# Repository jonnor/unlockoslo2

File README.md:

# Goals

* This is a development board. Should be safe to handle and easy to
  use.

## Non-goals

* Low-power operation

# Datasheets

* https://www.silabs.com/documents/public/data-sheets/cp2102n-datasheet.pdf
* https://www.silabs.com/documents/public/application-notes/an721.pdf

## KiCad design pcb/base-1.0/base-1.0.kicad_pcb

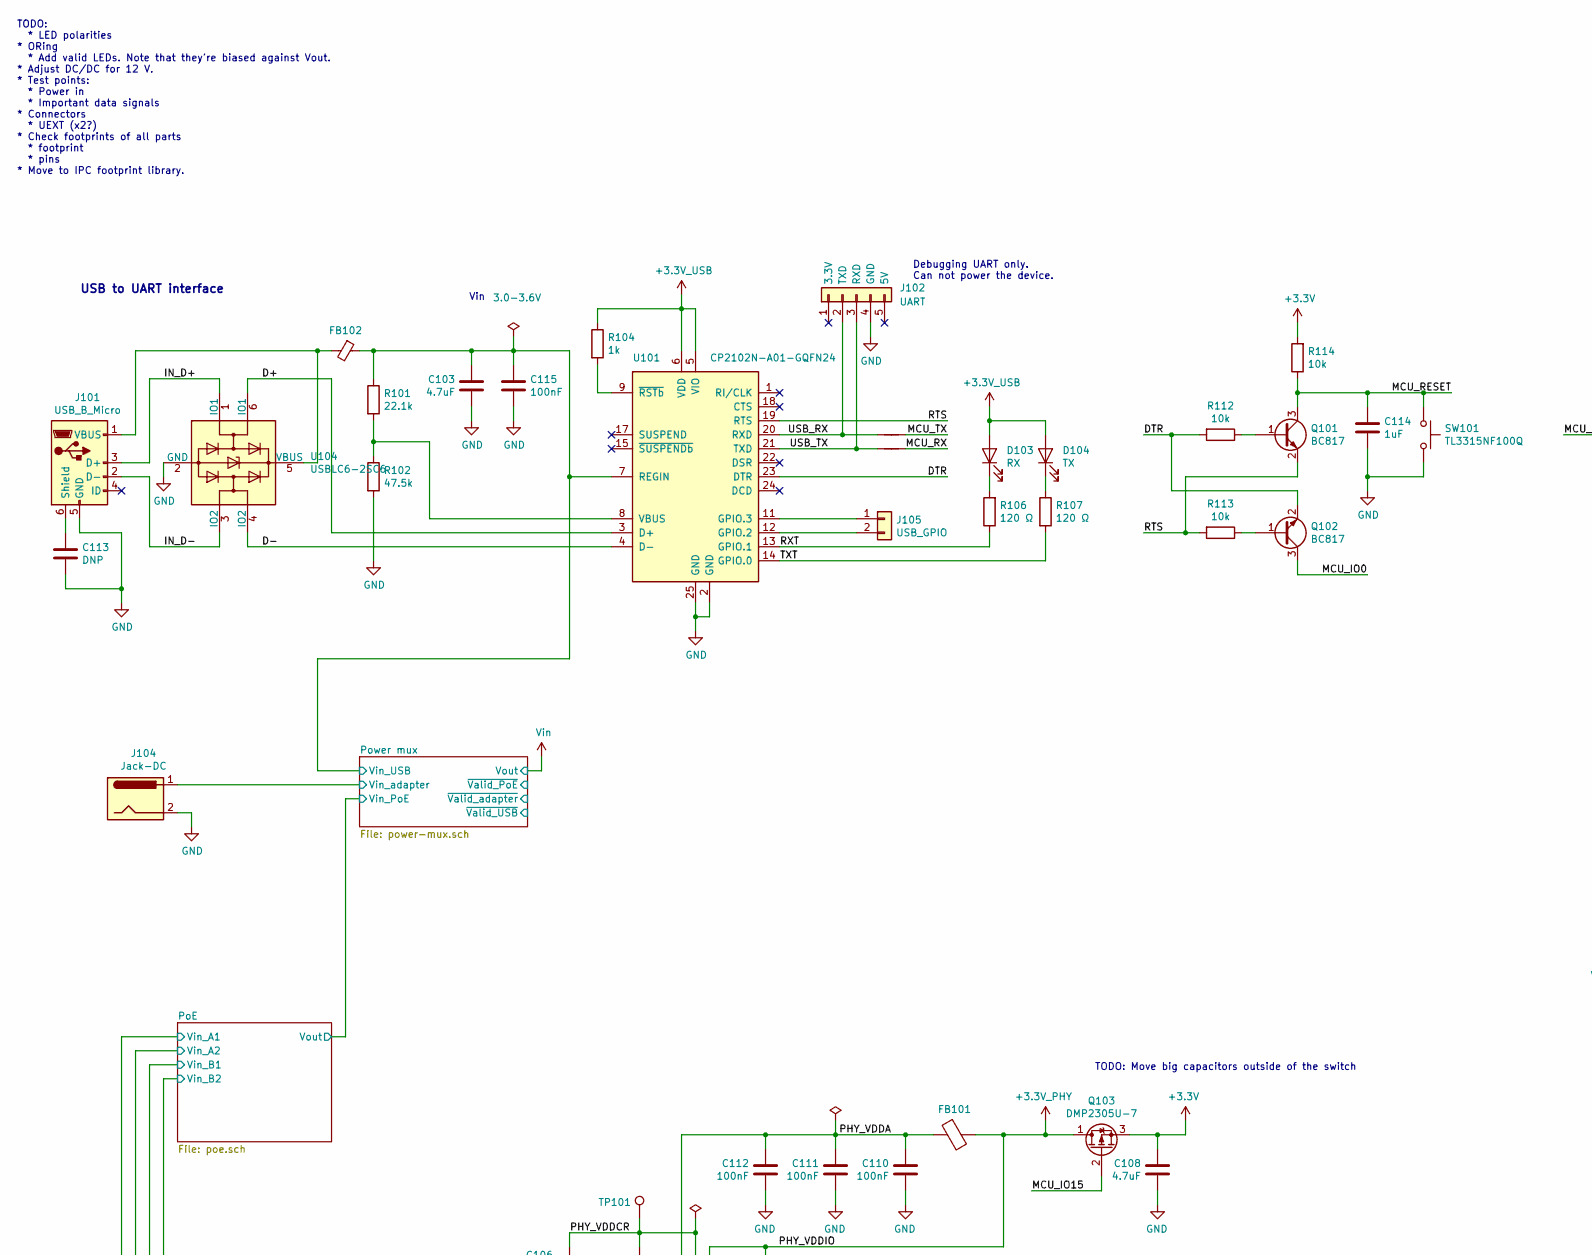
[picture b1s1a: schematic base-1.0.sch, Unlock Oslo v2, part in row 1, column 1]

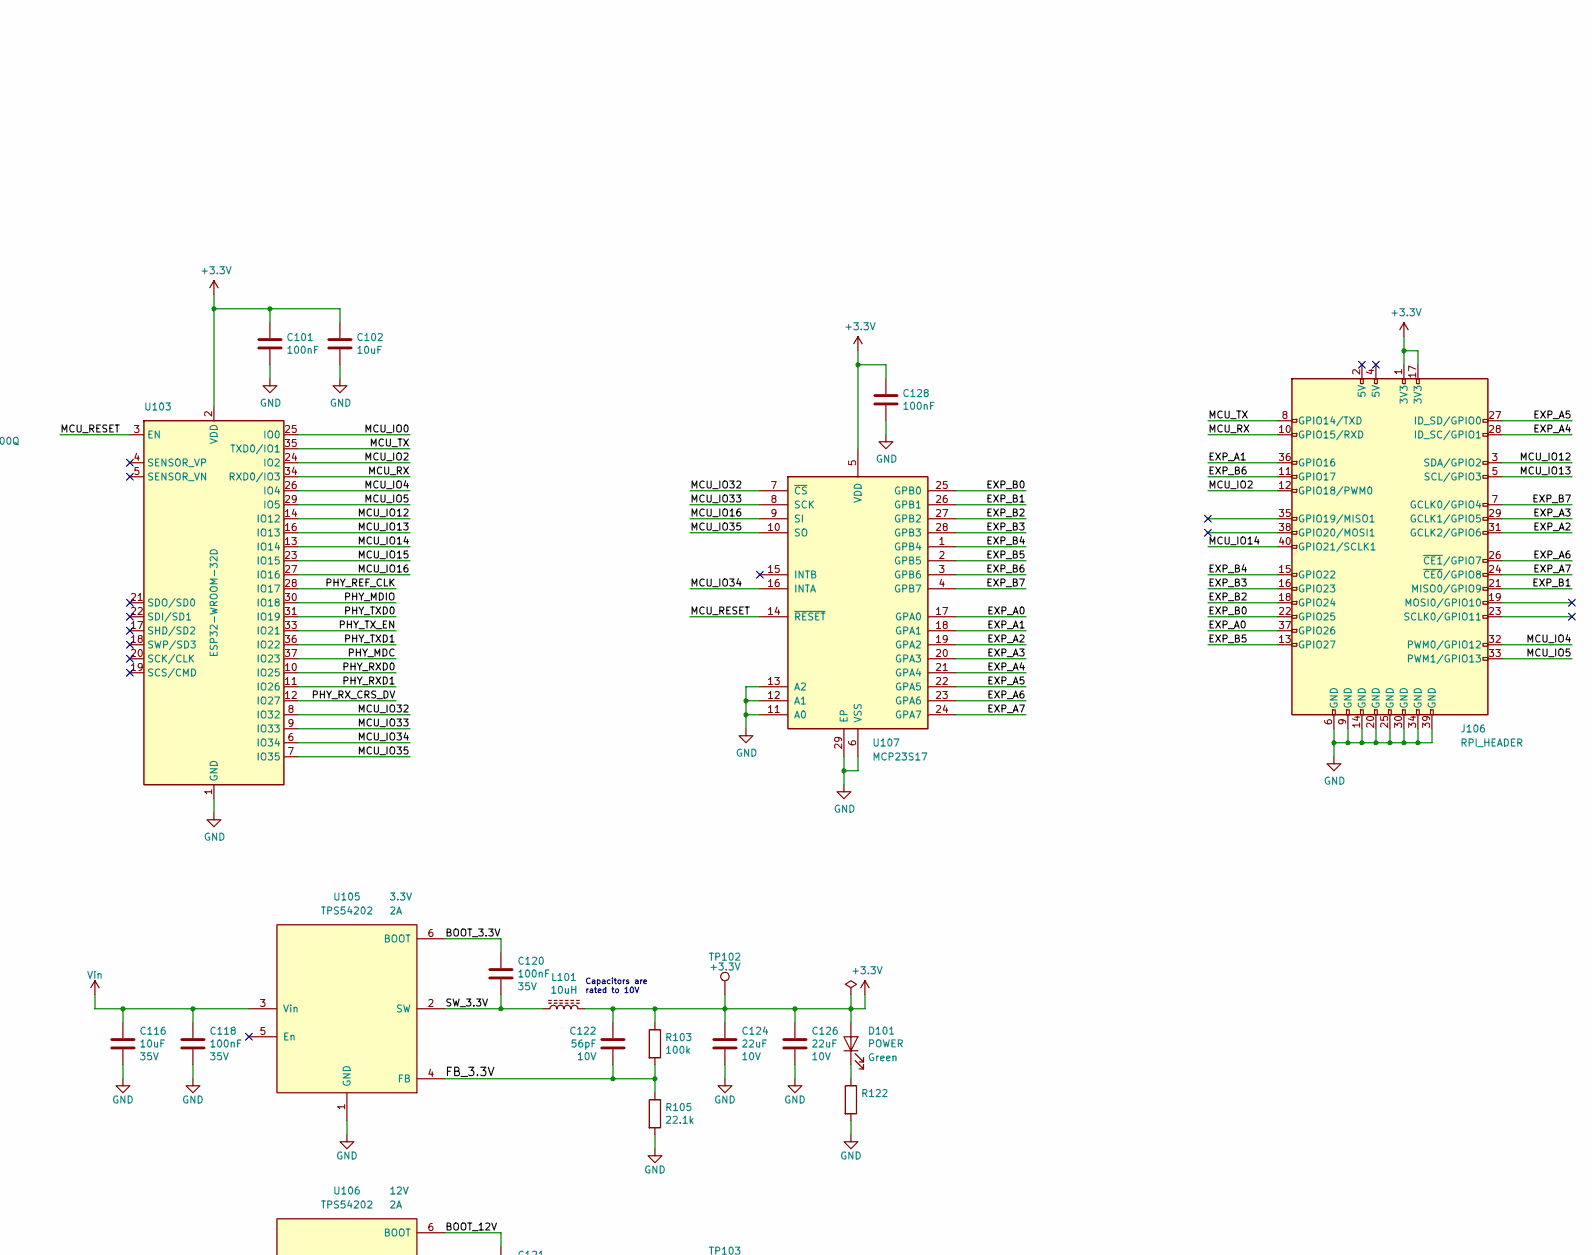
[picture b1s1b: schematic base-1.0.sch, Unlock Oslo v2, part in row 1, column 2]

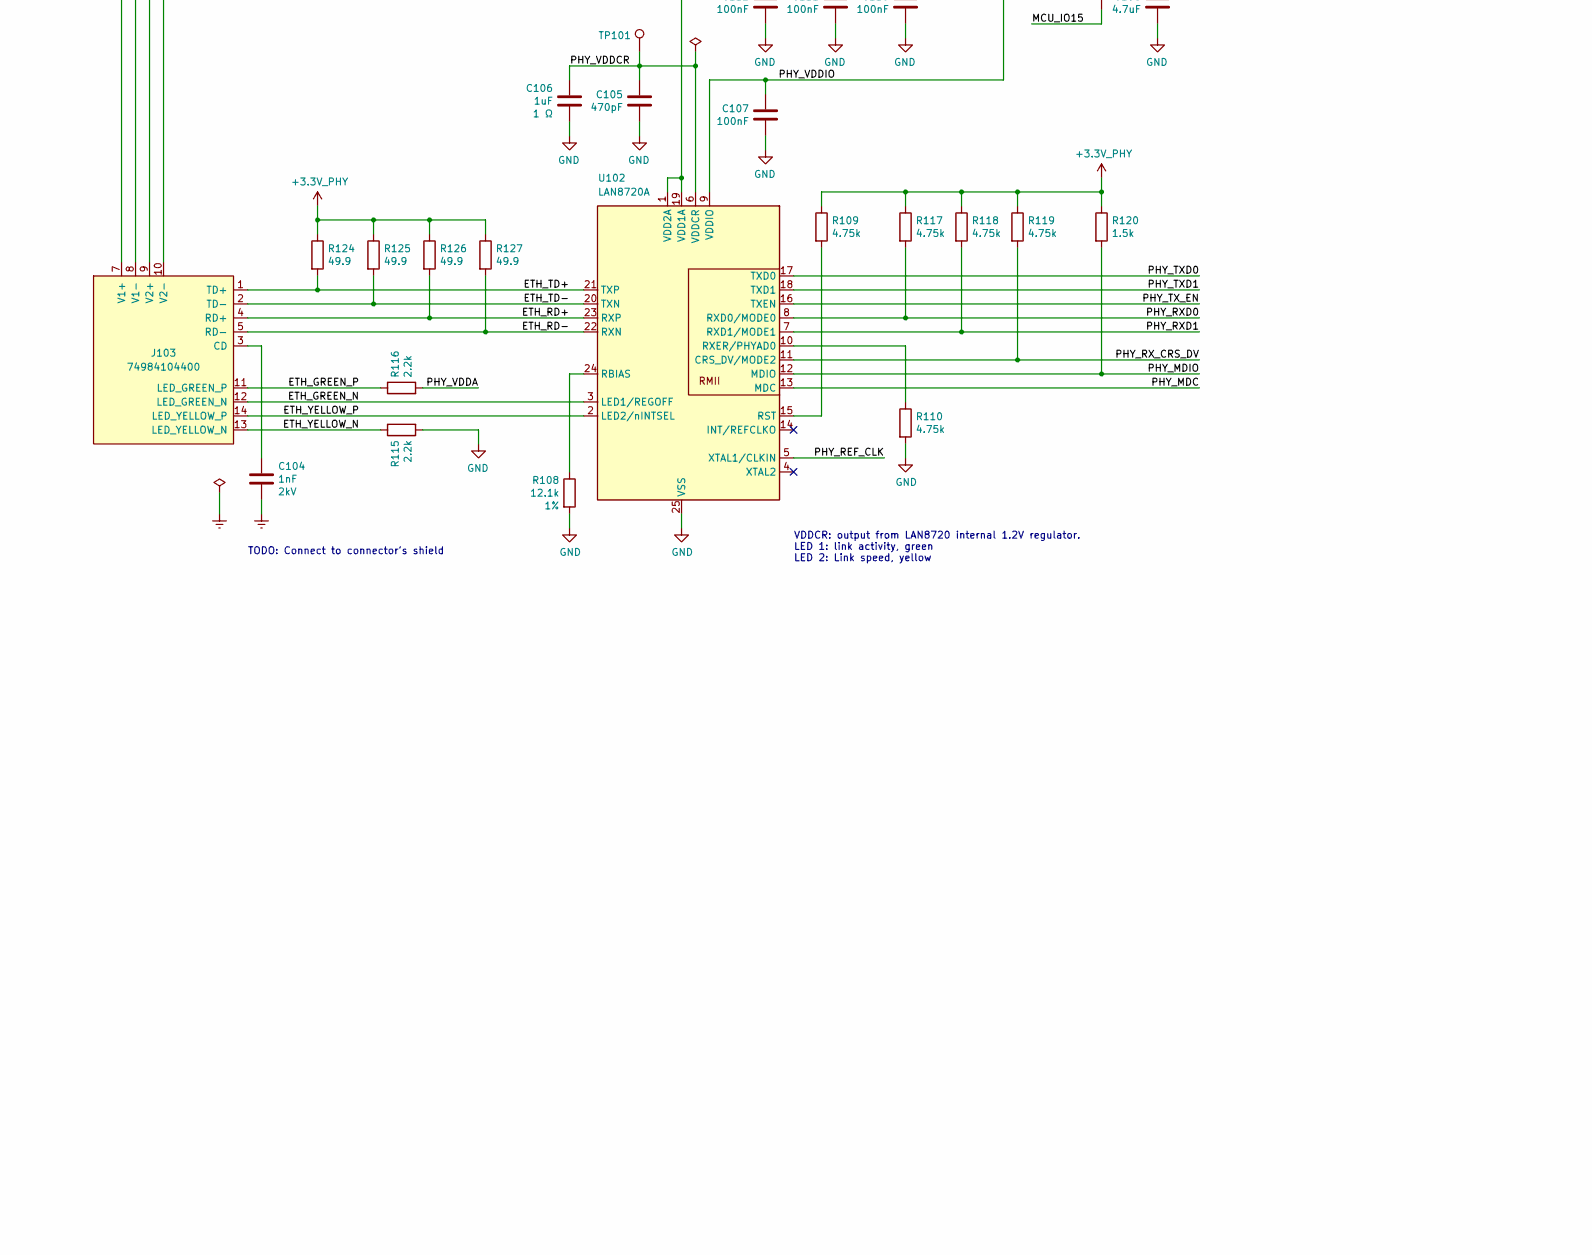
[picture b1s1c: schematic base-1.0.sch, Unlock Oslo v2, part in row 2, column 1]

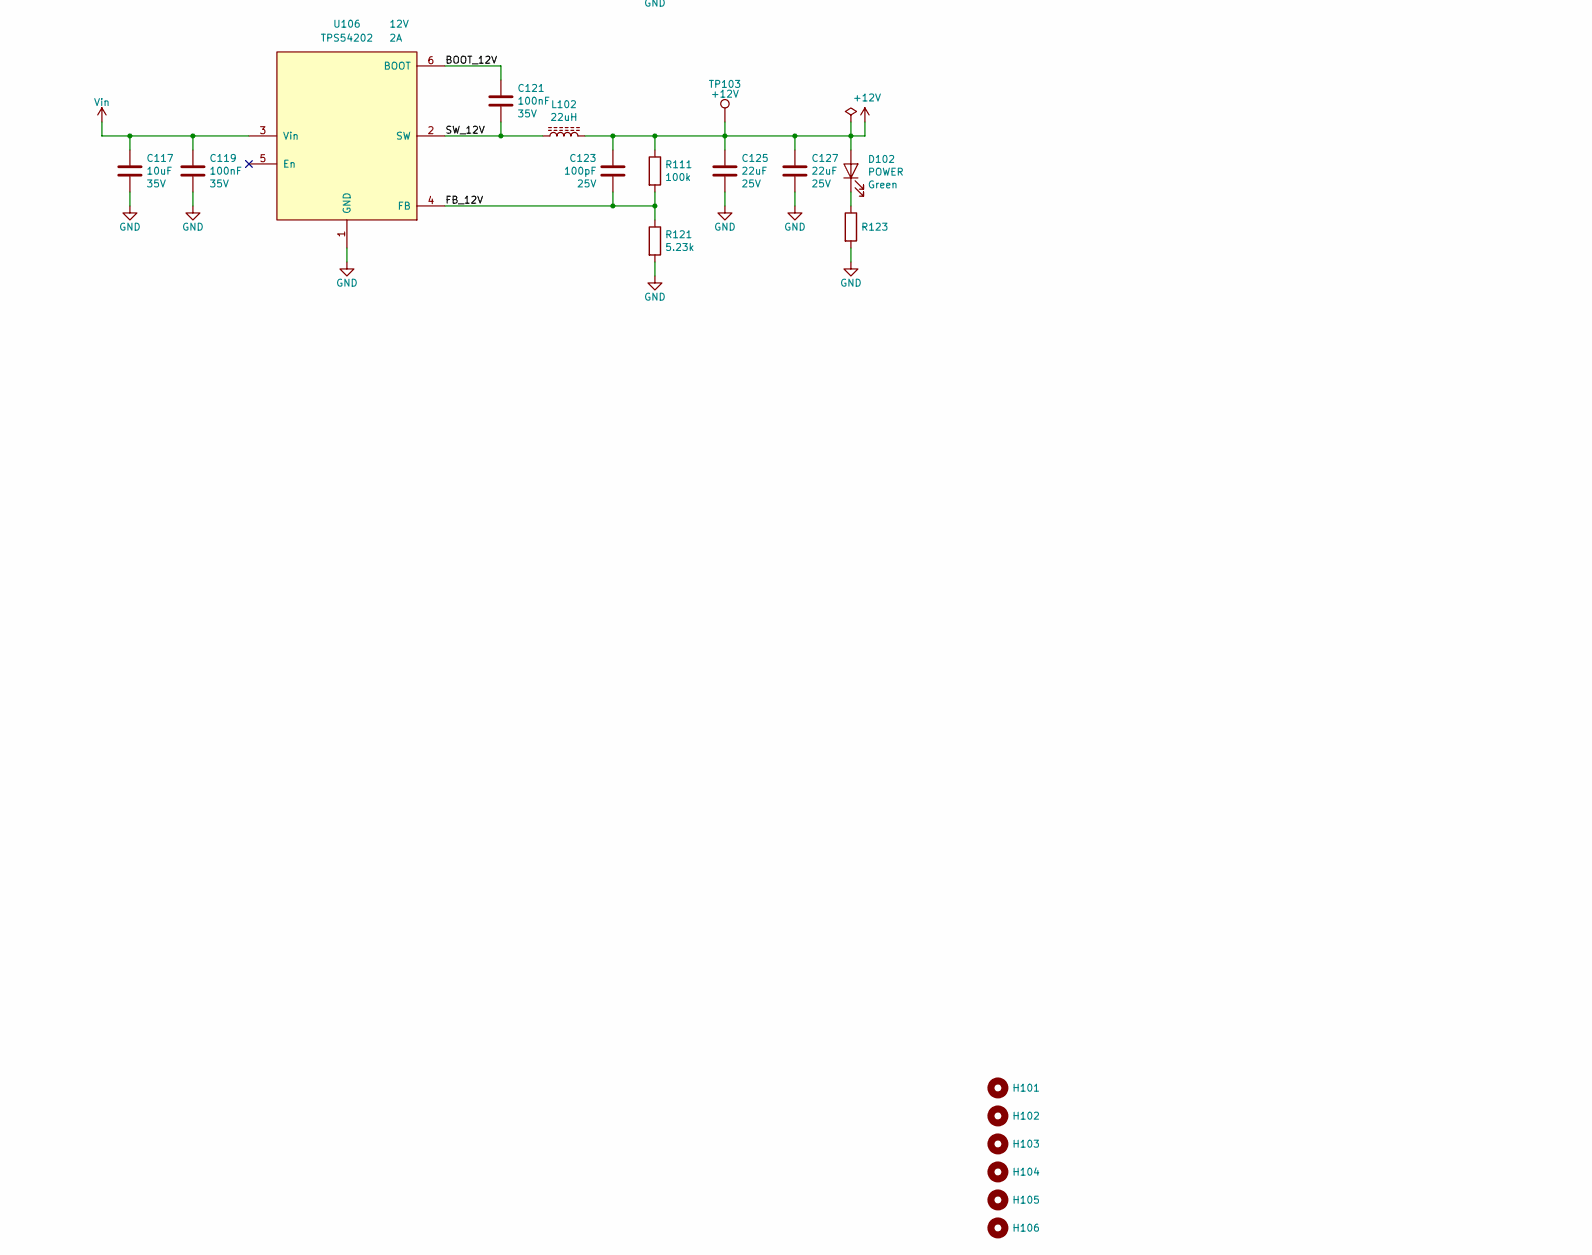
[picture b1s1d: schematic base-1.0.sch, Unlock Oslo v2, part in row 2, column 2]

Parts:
C101, C107, C110, C111, C112, C115: 100nF; CAPC_1005x015; mpn CL05B104KO5NNNC
C102: 10uF; CAPC_2012x040; mpn CL21B106KOQNNNE
C103, C108: 4.7uF; CAPC_1005x015; mpn CL05A475MQ5NRNC
C104: 1nF; CAPC_4532x040; Voltage 2kV; mpn C1812C102KGRACAUTO
C105: 470pF; CAPC_1005x015; mpn CL05B471JB5NNNC
C106, C114: 1uF; CAPC_1005x015; mpn CL05A105MQ5NNNC
C113: CAPC_1005x015
C116, C117: 10uF; CAPC_2012x040; Voltage 35V; mpn GMK212BBJ106KG-T
C118, C119, C120, C121: 100nF; CAPC_2012x040; Voltage 35V; mpn CL21B104MBCNNNC
C122: 56pF; CAPC_1005x015; Voltage 10V; mpn CL05C560JB5NNNC
C123: 100pF; CAPC_1005x015; Voltage 25V; mpn CL05C101JB5NNNC
C124, C126: 22uF; CAPC_2012x040; Voltage 10V; mpn CL21A226MQCLQNC
C125, C127: 22uF; CAPC_2012x040; Voltage 25V; mpn CL21A226MQCLQNC
C128: 100nF; CAPC_2012x040; mpn CL05B104KO5NNNC
D101, D102: POWER; LEDSC_3216x060; mpn CMD15-21VGD/TR8
D103: RX; LEDSC_3216x060; mpn SML-P12VTT86R
D104: TX; LEDSC_3216x060; mpn SML-P12VTT86R
FB101, FB102: FBMJ2125HS250NT; L_0805_2012Metric; mpn FBMJ2125HS250NT
H101, H102, H103, H104, H105, H106: MountingHole; MountingHole_2.5mm
J101: USB_B_Micro; 10118194; mpn 10118194-0001LF
J102: UART; PinHeader_1x06_P2.54mm_Vertical
J103: 74984104400
J104: Jack-DC; BarrelJack_CUI_PJ-063AH_Horizontal; mpn PJ-037AH-SMT-TR
J105: USB_GPIO; PinHeader_1x02_P2.54mm_Vertical
J106: RPI_HEADER; PinHeader_2x20_P2.54mm_Vertical; mpn PPPC202LFBN-RC
L101: 10uH; L_Taiyo-Yuden_NR-60xx; mpn NR6045T100M
L102: 22uH; L_Taiyo-Yuden_NR-80xx; mpn NRS8040T220MJGJ
NT101, NT102: Net-Tie_2; NetTie-2_SMD_Pad0.15mm
Q101, Q102: BC817; SOT-23; mpn BC817,235
Q103: DMP2305U-7; SOT-23; mpn DMP2305U-7
R101: 22.1k; RESC_1005x015
R102: 47.5k; RESC_1005x015
R103, R111: 100k; RESC_1005x015; mpn RC0402FR-07100KL
R104: 1k; RESC_1005x015
R105: 22.1k; RESC_1005x015; mpn RC0402FR-0713K3L
R106, R107: 120 Ω; RESC_1005x015
R108: 12.1k; RESC_1005x015; Tolerance 1%
R109, R110, R117, R118, R119: 4.75k; RESC_1005x015
R112, R113, R114: 10k; RESC_1005x015
R115, R116: 2.2k; RESC_1005x015
R120: 1.5k; RESC_1005x015
R121: 5.23k; RESC_1005x015; mpn RC0402FR-0713K3L
R122, R123: RESC_1005x015; mpn RC1005F561CS
R124, R125, R126, R127: 49.9; RESC_1005x015
SW101: TL3315NF100Q; TL3315
TP101: PHY_VDDCR; TestPoint_Pad_1.5x1.5mm
TP102: +3.3V; TestPoint_Pad_D1.0mm
TP103: +12V; TestPoint_Pad_D1.0mm
U101: CP2102N-A01-GQFN24; QFN-24-1EP_4x4mm_P0.5mm_EP2.6x2.6mm
U102: LAN8720A; QFN-24-1EP_4x4mm_P0.5mm_EP2.6x2.6mm
U103: ESP32-WROOM-32D; ESP32-WROOM-32
U104: USBLC6-2SC6; SOT-23-6
U105, U106: TPS54202; SOT-23-6
U107: MCP23S17; QFN-28-1EP_6x6mm_P0.65mm_EP4.25x4.25mm

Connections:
+3V3_PHY: C107.1, FB101.2, Q103.1 (D), R109.1, R117.1, R118.1, R119.1, R120.1, R124.1, R125.1, R126.1, R127.1, U102.9 (VDDIO)
+12V: C123.1, C125.1, C127.1, D102.2 (A), L102.1, R111.1, TP103.1
/BOOT_3.3V: C120.1, U105.6 (BOOT)
/BOOT_12V: C121.1, U106.6 (BOOT)
/D+: U101.3 (D+), U104.6 (IO1)
/D-: U101.4 (D-), U104.4 (IO2)
/DTR: Q102.2 (E), R112.2, U101.23 (DTR)
/ETH_GREEN_N: J103.12 (LED_GREEN_N), U102.3 (LED1/REGOFF)
/ETH_GREEN_P: J103.11 (LED_GREEN_P), R116.1
/ETH_RD+: J103.4 (RD+), R126.2, U102.23 (RXP)
/ETH_RD-: J103.5 (RD-), R127.2, U102.22 (RXN)
/ETH_TD+: J103.1 (TD+), R124.2, U102.21 (TXP)
/ETH_TD-: J103.2 (TD-), R125.2, U102.20 (TXN)
/ETH_YELLOW_N: J103.13 (LED_YELLOW_N), R115.1
/ETH_YELLOW_P: J103.14 (LED_YELLOW_P), U102.2 (LED2/nINTSEL)
/EXP_A0: J106.37 (GPIO26), U107.17 (GPA0)
/EXP_A1: J106.36 (GPIO16), U107.18 (GPA1)
/EXP_A2: J106.31 (GCLK2/GPIO6), U107.19 (GPA2)
/EXP_A3: J106.29 (GCLK1/GPIO5), U107.20 (GPA3)
/EXP_A4: J106.28 (ID_SC/GPIO1), U107.21 (GPA4)
/EXP_A5: J106.27 (ID_SD/GPIO0), U107.22 (GPA5)
/EXP_A6: J106.26 (~CE1~/GPIO7), U107.23 (GPA6)
/EXP_A7: J106.24 (~CE0~/GPIO8), U107.24 (GPA7)
/EXP_B0: J106.22 (GPIO25), U107.25 (GPB0)
/EXP_B1: J106.21 (MISO0/GPIO9), U107.26 (GPB1)
/EXP_B2: J106.18 (GPIO24), U107.27 (GPB2)
/EXP_B3: J106.16 (GPIO23), U107.28 (GPB3)
/EXP_B4: J106.15 (GPIO22), U107.1 (GPB4)
/EXP_B5: J106.13 (GPIO27), U107.2 (GPB5)
/EXP_B6: J106.11 (GPIO17), U107.3 (GPB6)
/EXP_B7: J106.7 (GCLK0/GPIO4), U107.4 (GPB7)
/FB_3.3V: C122.2, R103.2, R105.1, U105.4 (FB)
/FB_12V: C123.2, R111.2, R121.1, U106.4 (FB)
/IN_D+: J101.3 (D+), U104.1 (IO1)
/IN_D-: J101.2 (D-), U104.3 (IO2)
/MCU_IO0: Q102.3 (C), U103.25 (IO0)
/MCU_IO2: J106.12 (GPIO18/PWM0), U103.24 (IO2)
/MCU_IO4: J106.32 (PWM0/GPIO12), U103.26 (IO4)
/MCU_IO5: J106.33 (PWM1/GPIO13), U103.29 (IO5)
/MCU_IO12: J106.3 (SDA/GPIO2), U103.14 (IO12)
/MCU_IO13: J106.5 (SCL/GPIO3), U103.16 (IO13)
/MCU_IO14: J106.40 (GPIO21/SCLK1), U103.13 (IO14)
/MCU_IO15: Q103.2 (G), U103.23 (IO15)
/MCU_IO16: U103.27 (IO16), U107.9 (SI)
/MCU_IO32: U103.8 (IO32), U107.7 (~CS~)
/MCU_IO33: U103.9 (IO33), U107.8 (SCK)
/MCU_IO34: U103.6 (IO34), U107.16 (INTA)
/MCU_IO35: U103.7 (IO35), U107.10 (SO)
/MCU_RESET: C114.1, Q101.3 (C), R114.1, SW101.1, U103.3 (EN), U107.14 (~RESET~)
/MCU_RX: J106.10 (GPIO15/RXD), NT102.2, U103.34 (RXD0/IO3)
/MCU_TX: J106.8 (GPIO14/TXD), NT101.2, U103.35 (TXD0/IO1)
/PHY_MDC: U102.13 (MDC), U103.37 (IO23)
/PHY_MDIO: R120.2, U102.12 (MDIO), U103.30 (IO18)
/PHY_REF_CLK: U102.5 (XTAL1/CLKIN), U103.28 (IO17)
/PHY_RXD0: R117.2, U102.8 (RXD0/MODE0), U103.10 (IO25)
/PHY_RXD1: R118.2, U102.7 (RXD1/MODE1), U103.11 (IO26)
/PHY_RX_CRS_DV: R119.2, U102.11 (CRS_DV/MODE2), U103.12 (IO27)
/PHY_TXD0: U102.17 (TXD0), U103.31 (IO19)
/PHY_TXD1: U102.18 (TXD1), U103.36 (IO22)
/PHY_TX_EN: U102.16 (TXEN), U103.33 (IO21)
/PHY_VDDA: C110.1, C111.1, C112.1, FB101.1, R116.2, U102.1 (VDD2A), U102.19 (VDD1A)
/PHY_VDDCR: C105.1, C106.1, TP101.1, U102.6 (VDDCR)
/PoE/Vin_A1: J103.7 (V1+); also elsewhere on the board
/PoE/Vin_A2: J103.8 (V1-); also elsewhere on the board
/PoE/Vin_B1: J103.9 (V2+); also elsewhere on the board
/PoE/Vin_B2: J103.10 (V2-); also elsewhere on the board
/Power mux/Vin_USB: C103.2, C115.1, FB102.1, R101.1, U101.7 (REGIN); also elsewhere on the board
/Power mux/Vin_adapter: J104.1; also elsewhere on the board
/RTS: Q101.2 (E), R113.2, U101.19 (RTS)
/RXT: R106.1, U101.13 (GPIO.1)
/SW_3.3V: C120.2, L101.2, U105.2 (SW)
/SW_12V: C121.2, L102.2, U106.2 (SW)
/TXT: R107.2, U101.14 (GPIO.0)
/USB_RX: J102.2 (TXD), NT101.1, U101.20 (RXD)
/USB_TX: J102.3 (RXD), NT102.1, U101.21 (TXD)
Earth: C104.2
GND: C101.2, C102.2, C103.1, C105.2, C106.2, C107.2, C108.2, C110.2, C111.2, C112.2, C113.2, C114.2, C115.2, C116.2, C117.2, C118.2, C119.2, C124.2, C125.2, C126.2, C127.2, C128.2, J101.5 (GND), J102.4 (GND), J104.2, J106.6 (GND), J106.9 (GND), J106.14 (GND), J106.20 (GND), J106.25 (GND), J106.30 (GND), J106.34 (GND), J106.39 (GND), R102.2, R105.2, R108.2, R110.2, R115.2, R121.2, R122.2, R123.2, SW101.2, U101.2 (GND), U101.25 (GND), U102.25 (VSS), U103.1 (GND), U103.15 (GND), U103.38 (GND), U104.2 (GND), U105.1 (GND), U106.1 (GND), U107.6 (VSS), U107.11 (A0), U107.12 (A1), U107.13 (A2), U107.29 (EP); also elsewhere on the board
unnamed: C104.1, J103.3 (CD)
unnamed: C113.1, J101.6 (Shield)
unnamed: D101.1 (K), R122.1
unnamed: D102.1 (K), R123.1
unnamed: D103.1 (K), R106.2
unnamed: D104.1 (K), R107.1
unnamed: FB102.2, J101.1 (VBUS), U104.5 (VBUS)
unnamed: J105.1, U101.11 (GPIO.3)
unnamed: J105.2, U101.12 (GPIO.2)
unnamed: Q101.1 (B), R112.1
unnamed: Q102.1 (B), R113.1
unnamed: R101.2, R102.1, U101.8 (VBUS)
unnamed: R104.2, U101.9 (~RSTb)
unnamed: R108.1, U102.24 (RBIAS)
unnamed: R109.2, U102.15 (RST)
unnamed: R110.1, U102.10 (RXER/PHYAD0)
Vin: C116.1, C117.1, C118.1, C119.1, U105.3 (Vin), U106.3 (Vin); also elsewhere on the board

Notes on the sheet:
TODO: * LED polarities * ORing * Add valid LEDs. Note that they're biased against Vout. * Adjust DC/DC for 12 V. * Test points: * Power in * Important data signals * Connectors * UEXT (x2?) * Check footprints of all parts * footprint * pins * Move to IPC footprint library.
USB to UART interface
Vin
VDDCR: output from LAN8720 internal 1.2V regulator. LED 1: link activity, green LED 2: Link speed, yellow
Debugging UART only. Can not power the device.
Capacitors are rated to 10V
TODO: Connect to connector's shield
TODO: Move big capacitors outside of the switch

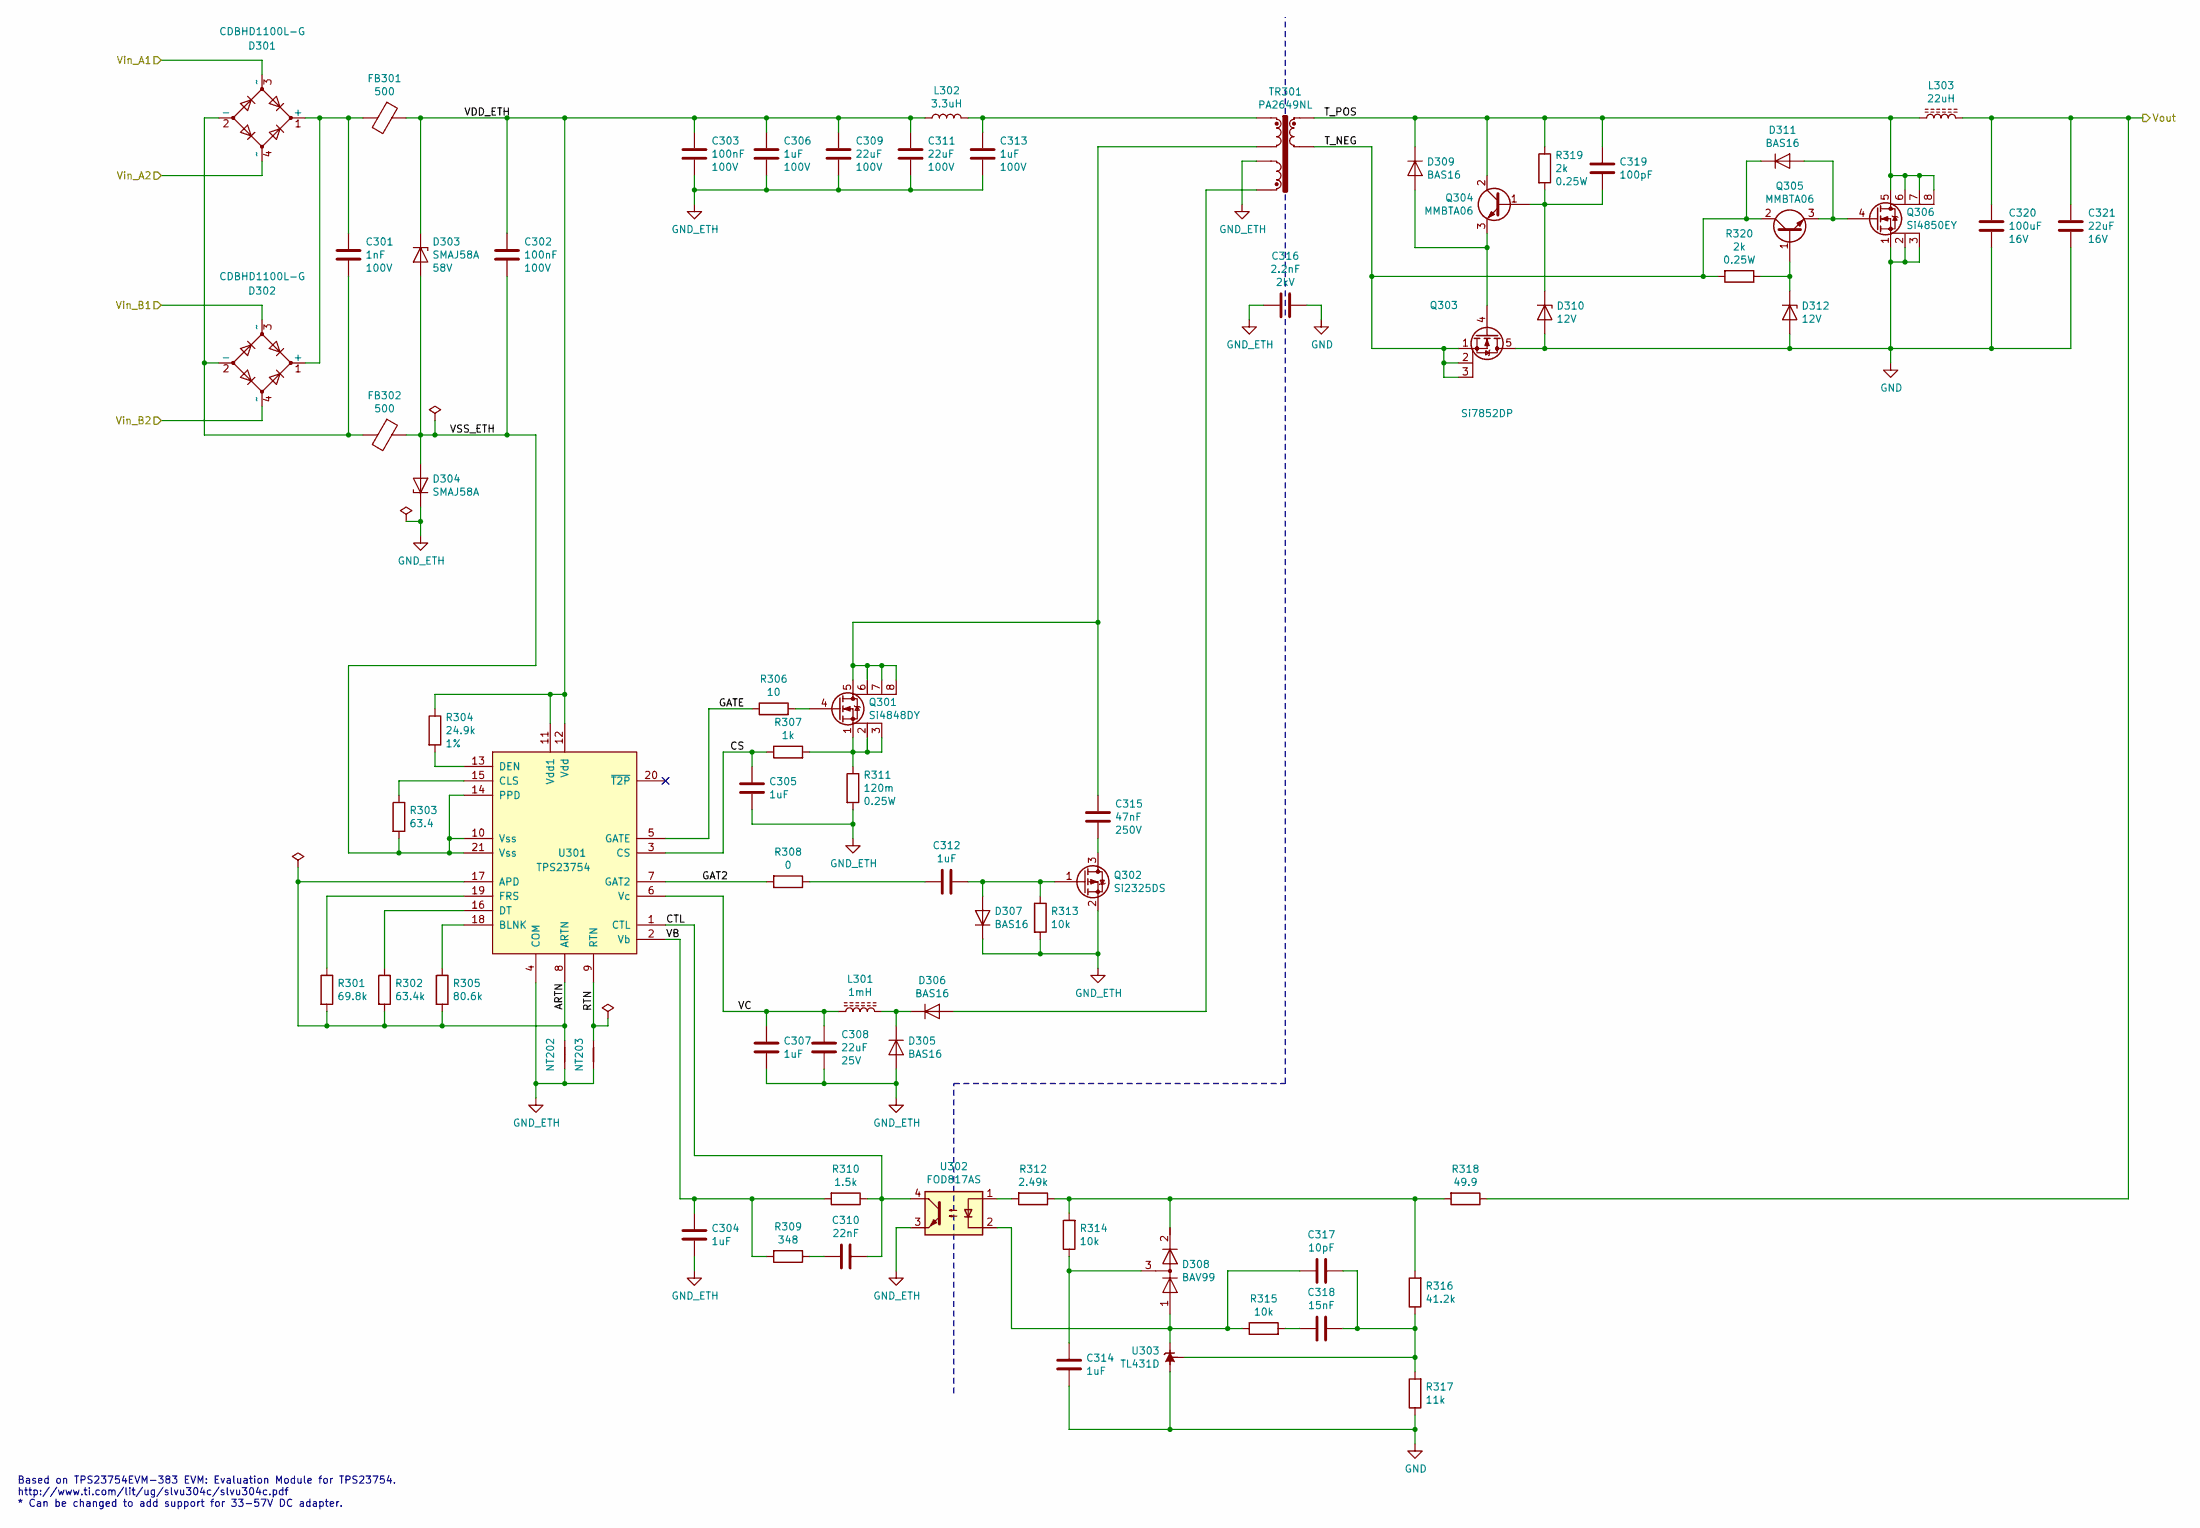
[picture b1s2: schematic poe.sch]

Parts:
C301: 1nF; CAPC_4532x040; Voltage 100V; mpn C1812C102KGRACAUTO
C302, C303: 100nF; CAPC_2012x040; Voltage 100V; mpn CL21B104KCFNNNE
C304, C305, C307, C312, C314: 1uF; CAPC_1005x015; mpn CL05A105MQ5NNNC
C306, C313: 1uF; CAPC_3216x040; Voltage 100V; mpn CL31B105KCHNFNE
C308: 22uF; CAPC_3216x040; Voltage 25V; mpn CL31A226KAHNNNE
C309, C311: 22uF; CP_Elec_8x10; Voltage 100V; mpn UUX2A220MNL6GS
C310: 22nF; CAPC_1005x015; mpn CL05B223KP5NNNC
C315: 47nF; CAPC_3216x040; Voltage 250V; mpn CL31B473KEHNNNE
C316: 2.2nF; CAPC_1005x015; Voltage 2kV; mpn CL05B222KB5NNNC
C317: 10pF; CAPC_1005x015; mpn CL05C100JB5NNNC
C318: 15nF; CAPC_1005x015; mpn CL05B153KO5NNNC
C319: 100pF; CAPC_1005x015; mpn CL05C101JB5NNNC
C320: 100uF; CP_Elec_8x10; Voltage 16V; mpn EEE-1EA101AP
C321: 22uF; CP_Elec_5x5.4; Voltage 16V; mpn 865080442004
D301, D302: CDBHD1100L-G; TO-269AA; mpn CDBHD1100L-G
D303: SMAJ58A; D_SMA; Voltage 58V; mpn SMAJ58A
D304: SMAJ58A; D_SMA; mpn SMAJ58A
D305, D306, D307, D309, D311: BAS16; D_SOD-323; mpn BAS16HT3G
D308: BAV99; SOT-23; mpn BAV99,235
D310, D312: 12V; D_SOT-23_ANK; mpn BZX84C12LT1G
FB301, FB302: 500; L_1206_3216Metric; mpn MI1206L501R-10
L301: 1mH; 74404043102A; mpn 74404043102A
L302: 3.3uH; 744043003; mpn 744043003
L303: 22uH; L_Taiyo-Yuden_NR-80xx; mpn NRS8040T220MJGJ
NT202, NT203: Net-Tie_2; NetTie-2_SMD_Pad0.20mm
Q301: Si4848DY; SO-8_3.9x4.9mm_P1.27mm; mpn SI4848DY-T1-E3
Q302: Si2325DS; SOT-23; mpn SI2325DS-T1-E3
Q303: Si7852DP; PowerPAK_SO-8_Single; mpn SI7852DP-T1-E3
Q304, Q305: MMBTA06; SOT-23; mpn MMBTA06-TP
Q306: Si4850EY; PowerIntegrations_SO-8; mpn SI4850EY-T1-E3
R301: 69.8k; RESC_1005x015
R302: 63.4k; RESC_1005x015
R303: 63.4; RESC_1005x015
R304: 24.9k; RESC_1005x015; Tolerance 1%
R305: 80.6k; RESC_1005x015
R306: 10; RESC_1005x015
R307: 1k; RESC_1005x015
R308: 0; RESC_1005x015
R309: 348; RESC_1005x015
R310: 1.5k; RESC_1005x015
R311: 120m; RESC_3216x040; mpn RL1206FR-070R12L
R312: 2.49k; RESC_1005x015
R313, R314, R315: 10k; RESC_1005x015
R316: 41.2k; RESC_1005x015
R317: 11k; RESC_1005x015
R318: 49.9; RESC_1005x015
R319, R320: 2k; RESC_3216x040
TR301: PA2649NL; PAxxxxNL; mpn PA2649NL
U301: TPS23754; HTSSOP-20-1EP_4.4x6.5mm_P0.65mm_EP3.4x6.5mm_Mask2.4x3.7mm
U302: FOD817AS; SMDIP-4_W9.53mm; mpn FOD817ASD
U303: TL431D; SOIC-8_3.9x4.9mm_P1.27mm

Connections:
/PoE/ARTN: NT202.1, R301.2, R302.2, R305.2, U301.8 (ARTN), U301.17 (APD)
/PoE/CS: C305.2, R307.1, U301.3 (CS)
/PoE/CTL: C310.1, R310.1, U301.1 (CTL), U302.4
/PoE/GAT2: R308.2, U301.7 (GAT2)
/PoE/GATE: R306.1, U301.5 (GATE)
/PoE/RTN: NT203.1, U301.9 (RTN)
/PoE/T_NEG: D311.1 (K), Q303.1 (S), Q303.2 (S), Q303.3 (S), Q305.2 (C), R320.2, TR301.9, TR301.10
/PoE/T_POS: C319.1, D309.1 (K), L303.1, Q304.2 (C), Q306.5 (D), Q306.6 (D), Q306.7 (D), Q306.8 (D), R319.1, TR301.6, TR301.7
/PoE/VB: C304.1, R309.2, R310.2, U301.2 (Vb)
/PoE/VC: C307.1, C308.1, L301.1, U301.6 (Vc)
/PoE/VDD_ETH: C302.1, C303.1, C306.1, C309.1, C311.1, D303.1 (K), FB301.1, L302.1, R304.1, U301.11 (Vdd1), U301.12 (Vdd)
/PoE/VSS_ETH: C302.2, D303.2 (A), D304.2 (A), FB302.1, R303.2, U301.10 (Vss), U301.14 (PPD), U301.21 (Vss)
/PoE/Vin_A1: D301.3 (~~); also elsewhere on the board
/PoE/Vin_A2: D301.4 (~~); also elsewhere on the board
/PoE/Vin_B1: D302.3 (~~); also elsewhere on the board
/PoE/Vin_B2: D302.4 (~~); also elsewhere on the board
/Power mux/Vin_PoE: C320.1, C321.1, L303.2, R318.1; also elsewhere on the board
GND: C314.2, C316.1, C320.2, C321.2, D310.2 (A), D312.2 (A), Q303.5 (D), Q306.1 (S), Q306.2 (S), Q306.3 (S), R317.1, U303.2 (A), U303.3 (A), U303.6 (A), U303.7 (A); also elsewhere on the board
GND_ETH: C303.2, C304.2, C305.1, C306.2, C307.2, C308.2, C309.2, C311.2, C313.2, C316.2, D304.1 (K), D305.2 (A), D307.1 (K), NT202.2, NT203.2, Q302.2 (S), R311.2, R313.2, TR301.4, U301.4 (COM), U302.3
unnamed: C301.1, D301.1 (+), D302.1 (+), FB301.2
unnamed: C301.2, D301.2 (-), D302.2 (-), FB302.2
unnamed: C310.2, R309.1
unnamed: C312.1, D307.2 (A), Q302.1 (G), R313.1
unnamed: C312.2, R308.1
unnamed: C313.1, L302.2, TR301.1
unnamed: C314.1, D308.3 (common), R314.1
unnamed: C315.1, Q302.3 (D)
unnamed: C315.2, Q301.5 (D), Q301.6 (D), Q301.7 (D), Q301.8 (D), TR301.2
unnamed: C317.1, C318.1, R316.1, R317.2, U303.8 (REF)
unnamed: C317.2, D308.1 (A), R315.1, U302.2, U303.1 (K)
unnamed: C318.2, R315.2
unnamed: C319.2, D310.1 (K), Q304.1 (B), R319.2
unnamed: D305.1 (K), D306.1 (K), L301.2
unnamed: D306.2 (A), TR301.5
unnamed: D308.2 (K), R312.1, R314.2, R316.2, R318.2
unnamed: D309.2 (A), Q303.4 (G), Q304.3 (E)
unnamed: D311.2 (A), Q305.3 (E), Q306.4 (G)
unnamed: D312.1 (K), Q305.1 (B), R320.1
unnamed: Q301.1 (S), Q301.2 (S), Q301.3 (S), R307.2, R311.1
unnamed: Q301.4 (G), R306.2
unnamed: R301.1, U301.19 (FRS)
unnamed: R302.1, U301.16 (DT)
unnamed: R303.1, U301.15 (CLS)
unnamed: R304.2, U301.13 (DEN)
unnamed: R305.1, U301.18 (BLNK)
unnamed: R312.2, U302.1

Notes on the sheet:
Based on TPS23754EVM-383 EVM: Evaluation Module for TPS23754. http://www.ti.com/lit/ug/slvu304c/slvu304c.pdf * Can be changed to add support for 33-57V DC adapter.
